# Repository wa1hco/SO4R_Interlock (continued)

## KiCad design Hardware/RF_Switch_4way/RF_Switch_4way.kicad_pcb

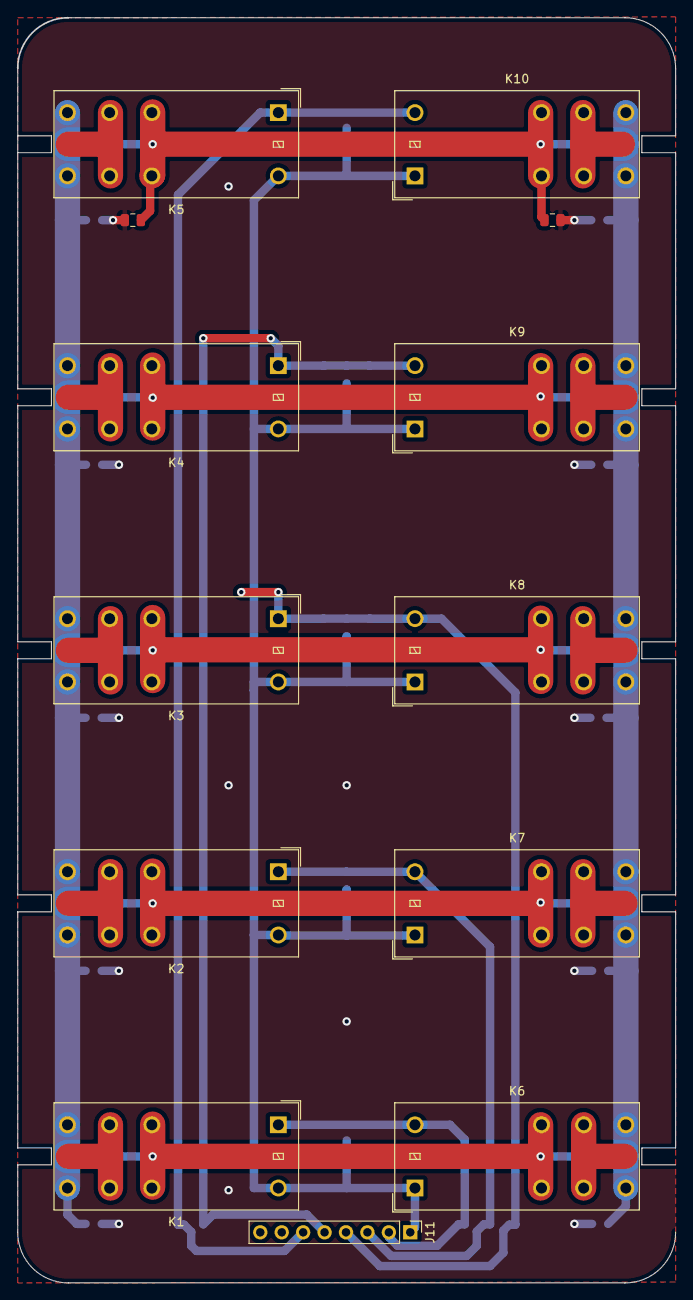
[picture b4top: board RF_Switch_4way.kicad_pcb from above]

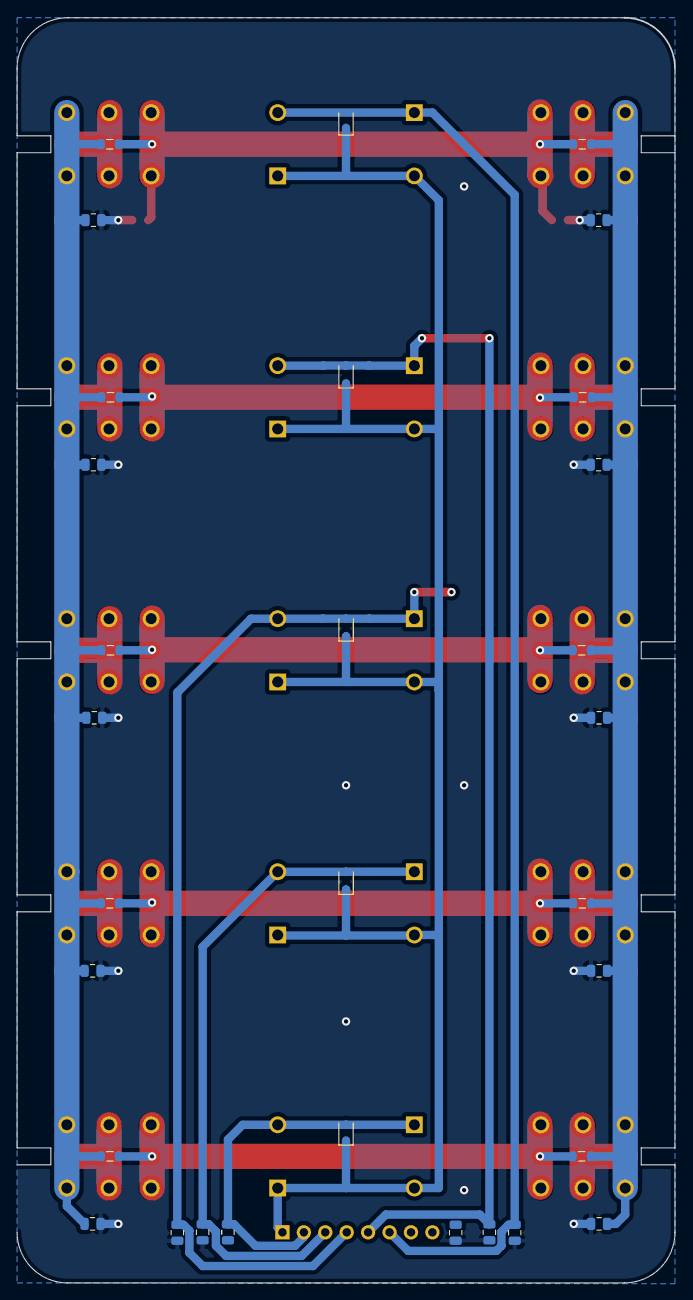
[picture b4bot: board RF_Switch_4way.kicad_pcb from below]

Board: 2 copper layers, 78.0 x 150.0 mm, 44 parts (31 on the bottom side), 14 nets.

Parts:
C1, C2, C3, C4, C5, C9, C10, C18, C20, C21, C22, C24: 5p; C_0805_2012Metric
C6, C7, C8, C14, C15, C16: .01; C_0805_2012Metric
D1, D2, D3, D4, D5: D; D_SOD-323
J11: Conn_01x08_Pin; PinHeader_1x08_P2.54mm_Vertical
K1, K2, K3, K4, K5, K6, K7, K8, K9, K10: G2RL-1-E; Relay_SPDT_Omron_G2RL-1-E
L1, L2, L3, L4, L5, L6, L7, L8, L9, L10: L_Small; L_0805_2012Metric

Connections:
/12V: C14.1, D1.1 (K), D2.1 (K), D3.1 (K), D4.1 (K), D5.1 (K), J11.1, K1.A2, K2.A2, K3.A2, K4.A2, K5.A2, K6.A1, K7.A1, K8.A1, K9.A1, K10.A1
/Amplifier\: C15.1, D5.2 (A), J11.6, K5.A1, K10.A2
/Radio_1\: C8.1, D1.2 (A), J11.2, K1.A1, K6.A2
/Radio_2\: C7.1, D2.2 (A), J11.3, K2.A1, K7.A2
/Radio_3\: C6.1, D3.2 (A), J11.4, K3.A1, K8.A2
/Radio_4\: C16.1, D4.2 (A), J11.5, K4.A1, K9.A2
GND: C1.2, C2.2, C3.2, C4.2, C5.2, C6.2, C7.2, C8.2, C9.2, C10.2, C14.2, C15.2, C16.2, C18.2, C20.2, C21.2, C22.2, C24.2
unnamed: C1.1, C2.1, C3.1, C4.1, C5.1, K6.14, K7.14, K8.14, K9.14, K10.14, L1.1, L2.1, L3.1, L4.1, L5.1
unnamed: C9.1, C10.1, K5.12, K10.12, L5.2, L10.1
unnamed: C18.1, C20.1, C21.1, C22.1, C24.1, K1.14, K2.14, K3.14, K4.11, K4.14, K5.14, L6.2, L7.2, L8.2, L9.2, L10.2
unnamed: K1.12, K6.12, L1.2, L6.1
unnamed: K2.12, K7.12, L2.2, L7.1
unnamed: K3.12, K8.12, L3.2, L8.1
unnamed: K4.12, K9.12, L4.2, L9.1

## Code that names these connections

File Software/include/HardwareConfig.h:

#ifndef HardwareConfig_h
#define HardwareConfig_h
// Hardware configuration from the V1 schematic
#include <Arduino.h> // get the pin names

// AVR32DB48, Hardware Pin Definitions, lower case means secondary pin location
//-----|--------|----------|------|-------|--------|-------|-----|--------|--------|
// Pin | Name   | Function | Free | Power | Serial | ADC   | DAC |  SPI   |  TWI   |
//-----|--------|----------|------|-------|--------|-------|-----|--------|--------|
//  1  | PA5    |          | PA5  |       | 0,rxd  |       |     |        |        |
//  2  | PA6    | RTS4\    |      |       | 0,xck  |       |     | 0,MOSI |        |
//  3  | PA7    | CTS4\    |      |       | 0,xdir |       |     | 0,MISO |        |
//  4  | PB0    | RTS3\    |      |       | 3,TXD  |       |     | 0,SCK  |        |
//  5  | PB1    | CTS3\    |      |       | 3,RXD  |       |     | 0,SS\  |        |
//  6  | PB2    | CTS2\    |      |       | 3,XCK  |       |     |        | 1,sda  |
//  7  | PB3    | RTS2\    |      |       | 3,XDIR |       |     |        | 1,scl  |
//  8  | PB4    | RTS1\    |      |       | 3,txd  |       |     |        |        |
//  9  | PB5    | DEN      |      |       | 3,rxd  |       |     |        |        |
// 10  | PC0    | DSEL0    |      |       | 1,TXD  |       |     |        |        |
// 11  | PC1    | DSEL1    |      |       | 1,RXD  |       |     |        |        |
// 12  | PC2    | RLYYEL   |      |       | 1,XCK  |       |     |        | 0,sda  |
//-----|--------|----------|------|-------|--------|-------|-----|--------|--------|
// 13  | PC3    | RLY1     |      |       | 1,XDIR |       |     |        | 0,scl  |
// 14  | VDDIO2 |          |      | 5V    |        |       |     |        |        |
// 15  | GND    |          |      | GND   |        |       |     |        |        |
// 16  | PC4    | RLY2     |      |       | 1,txd  |       |     |        |        |
// 17  | PC5    | RLY3     |      |       | 1,rxd  |       |     |        |        |
// 18  | PC6    | RLY4     |      |       | 1,xck  |       |     |        | 0,sda  |
// 19  | PC7    | RLYGRN   |      |       | 1,xdir |       |     |        | 0,sda  |
// 20  | PD0    | RIG1YEL  |      |       |        | AIN0  |     |        |        |
// 21  | PD1    | SPR1     |      |       |        | AIN1  |     |        |        |
// 22  | PD2    | KEY1\M   |      |       |        | AIN2  |     |        |        |
// 23  | PD3    | PTT1     |      |       |        | AIN3  |     |        |        |
// 24  | PD4    | RIG1GRN  |      |       |        | AIN4  |     |        |        |
//-----|--------|----------|------|--=----|--------|-------|-----|--------|--------|
// 25  | PD5    | RIG2YEL  |      |       |        | AIN5  |     |        |        |
// 26  | PD6    | SPR2     |      |       |        | AIN6  | OUT |        |        |
// 27  | PD7    | KEY2\M   |      |       |        | AIN7  |     |        |        |
// 28  | AVDD   |          |      | 5V    |        |       |     |        |        |
// 29  | AGND   |          |      | GND   |        |       |     |        |        |
// 30  | PE0    | PTT2     |      |       | 4,TXD  | AIN8  |     | 0,mosi |        |
// 31  | PE1    | IS       |      |       | 4,RXD  | AIN9  |     | 0,miso |        |
// 32  | PE2    |          | PE2  |       | 4,XCK  | AIN10 |     | 0,sck  |        |
// 33  | PE3    | RIG3YEL  |      |       | 4,XDIR | AIN11 |     | 0,ss\  |        |
// 34  | PF0    | SPR3     |      |       | 2,TXD  |       |     |        |        |
// 35  | PF1    | KEY3\M   |      |       | 2,RXD  |       |     |        |        |
// 36  | PF2    | PTT3     |      |       | 2,XCK  |       |     |        | 1,SDA  |
//-----|--------|----------|------|-------|--------|-------|-----|--------|--------|
// 37  | PF3    |          | PF3  |       | 2,XDIR |       |     |        | 1,SCL  |
// 38  | PF4    |          | PF4  |       | 2,txd  |       |     |        |        |
// 39  | PF5    | RIG4YEL  |      |       | 2,rxd  |       |     |        |        |
// 40  | PF6    | RESET    |      | RESET |        |       |     |        |        |
// 41  | UPDI   | UPDI     |      | UPDI  |        |       |     |        |        |
// 42  | VDD    | 5V       |      | 5V    |        |       |     |        |        |
// 43  | GND    | GND      |      | GND   |        |       |     |        |        |
// 44  | PA0    | TXD_M    |      |       | 0,TXD  |       |     |        |        |
// 45  | PA1    | RXD_M    |      |       | 0,RXD  |       |     |        |        |
// 46  | PA2    | SPR4     |      |       | 0,XCK  |       |     |        | 0,SDA  |
// 47  | PA3    | KEY4\M   |      |       | 0,XDIR |       |     |        | 0,SCL  |
// 48  | PA4    | PTT4     |      |       | 0,txd  |       |     |        |        |
//-----|--------|----------|------|-------|--------|-------|-----|--------|--------|


// Define connections to USB Serial ports
//      PinName     Port Name  TQFP48  Function
#define RTS1nPIN    PIN_PB4    //  8   input,  low true
#define RTS2nPIN    PIN_PB3    //  7   input,  low true
#define RTS3nPIN    PIN_PB0    //  4   input,  low true
#define RTS4nPIN    PIN_PA6    //  2   input,  low true

//#define CTS1nPIN    PIN_PC0    // 14   output, low true
#define CTS2nPIN    PIN_PB2    //  6   output, low true
#define CTS3nPIN    PIN_PB1    //  5   output, low true
#define CTS4nPIN    PIN_PA7    //  3   output, low true

// Define connections to rigs
//      PinName     Port Name  TQFP48  Function
#define KEY1nPIN    PIN_PD2    // 22   input,  low true,  radio keyed
#define KEY2nPIN    PIN_PD7    // 27 
#define KEY3nPIN    PIN_PF1    // 35
#define KEY4nPIN    PIN_PA3    // 47

#define PTT1PIN     PIN_PD3    // 23   output, high true, key radio
#define PTT2PIN     PIN_PE0    // 30
#define PTT3PIN     PIN_PF2    // 36
#define PTT4PIN     PIN_PA4    // 48

#define SPR1PIN     PIN_PD1    // 21   input/output, TBD function
#define SPR2PIN     PIN_PD6    // 26
#define SPR3PIN     PIN_PF0    // 34
#define SPR4PIN     PIN_PA2    // 46

// Define LEDs on RJ-45 rig interface jack
// Green LEDs for each radio mean radio transmitting
// Radio 1 (SSB/CW) indication comes from its KEY output
// Radios 2, 3, 4 (FT8) come from the PTT lines
//      PinName     Port Name  TQFP48  Function
#define RIG1GRNPIN  PIN_PD4    // 24   output, high true, radio keyed

// Yellow LEDs for each radio mean radio wants to Tx but inhibited
#define RIG1YELPIN  PIN_PD0    // 20   output, high true, radio inhibited
#define RIG2YELPIN  PIN_PD5    // 25
#define RIG3YELPIN  PIN_PE3    // 33
#define RIG4YELPIN  PIN_PF5    // 39

// Define connection to relays
#define RLY1PIN     PIN_PC3    // 13   output, high true
#define RLY2PIN     PIN_PC4    // 16   output, high true
#define RLY3PIN     PIN_PC5    // 17   output, high true
#define RLY4PIN     PIN_PC6    // 18   output, high true

// Define connections to LEDs on RJ-45 relay interface JACK
#define RLYYELPIN   PIN_PC2    // 12   output, high true
#define RLYGRNPIN   PIN_PC7    // 19   output, high true

// Define connections to BTS5200 relay driver
#define DENPIN      PIN_PB5    // Data Enable
#define DSEL0PIN    PIN_PC0    // Data Select
#define DSEL1PIN    PIN_PC1     
#define ISPIN       PIN_PE1    // Analog from BTS5300

// Public function
void ConfigPins();

#endif

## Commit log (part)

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2025-07-03 initial commit of design for discussion
2025-07-04 Moved 4:1 up a level
2025-07-11 Ordered V1 of Transfer Relay boards and Interlock boards and assembly
2025-07-13 started V2 of hardware board Started software development
2025-07-17 Hardware better names for PDF in documentation area started on V2 of hardware Connected reset\ to VDD on MCU added .lck to .gitignore Software improves reading RTS and KEY inputs all at one writing K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
    Relay signals derived from KEY and priority
2025-07-17 Updated README for clarity and current design
2025-07-23 reversed the RJ45 connectors
2025-07-23 copied software from main branch
2025-07-24 Added drilling dimensions for Transfer Relay enclosure Added ethernet cable color codes to schematic, validated that part Validated KEY/ input to interlock works Validated KEY/ input inhibits lower p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
2025-07-26 Added code to control LEDs on relay connector Green LED if any Tx Yellow LED if any Tx inhibited
2025-07-28 V2 Files sent to JLCPCB Relays are driven by 12V Relay driver has diagnostic interface to MCU Diode combine 12V from rig interface or barrel jack
2025-07-28 2nd try at submitting to JLCPBC, this is hardware V2.1 V2 added BTS5200 relay driver chip, 4 channels Corrected footprints Adjusted HardwareConfig.h to adapt to new pins related to adding relay drive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
2025-07-30 Merged in some changes from the V2 branch
2025-08-04 replacing through holes with surface pads for RF to coax center pin wires
2025-08-04 started add code to interface with relay driver
2025-08-10 Fix problem with 3.6V input protection zener leaking too much for input pullups, changed to 4V7 zener. initialize for loop index which was causing strange problems Fix labeling of RJ45 LED colors
2025-08-10 Serial works Removed serial test code Updated description on Schematic
2025-08-12 Document the cables interfacing SO4R_Interlock with rigs
2025-08-12 Update README.md
    separate readme for each branch
2025-08-12 move datasheets into Datasheets directory
2025-08-12 Renamed LED signals for clarity Matching changes in Software and Hardware name
2025-08-12 comment type fix
2025-08-12 More comment tweaks
2025-08-14 Add PTT and CAT connectors on Radio Interface Cables Mark pins as unused
2025-08-14 Add Radio Interface Cables
2025-08-16 Added LibreOffice Impress file describing design and use
2025-08-16 Added pdf version of design presentation
2025-08-17 Update code to prevent sequencing error if user hits radio's TX on WSJT radios Update documentation
2025-08-17 Manually merged git branch V2 into main
2025-08-26 updated documentation
2025-08-26 starting to merge V2 into main
2025-09-11 Updated slide presentation
2025-09-23 Converted Radio 4 PTT to amplifier key line.
2025-09-24 New board layout for Polycase EX-63 USB and Ethernet cables route out the back panel Indicator on front panel Adjusted hardware definition file for new MCU pinout
2025-09-24 still laying out pcb
2025-09-25 PCB layout ready for checking
2025-10-07 Combined transfer and Mux into a single board Two boards needed for system - rig to amp in - amp out to antenna
2026-01-31 Updated presentation using LibreOffice Tweaked appearance of schematic Added datasheets
2026-02-01 minor tweaks to schematic for appearance Added some datasheets Deleted some unused kicad designs directory trees
2026-05-15 SO-239 mount directly to the bottom of the pcb, so large hole and jumper to pad
2026-05-15 Add Transfer_Switch_Quad hardware and updated footprints; update .gitignore
2026-05-15 removed an obsolete board
2026-05-15 Remove obsolete Transfer_G2RL hardware project
